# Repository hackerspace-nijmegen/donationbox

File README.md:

# donationbox

Arduino code was developed using plastformio. If you don't know it, I strongly recommend you to give it a try. If you just was to get this running quickly you can copy and paste the contents of main.cpp into the arduino ide. It is completely compatible. 

## Dependencies:
Arduino code depends on the [LowPower](https://github.com/rocketscream/Low-Power) library

## Circuit boards:
There is a double sided (arduinoshield) and a single sided version (arduinoshield-ss) of the same schematic. KiCad did not allow me to share the schematic between two boards so there is some duplication.
Neither is actually a shield. It's just a breakout board for a transistor switched led strip and two ir endstops. 

## Todo's:
* make a fancy animation (using pwm?) on the led instead of the current dump on/off sequence.

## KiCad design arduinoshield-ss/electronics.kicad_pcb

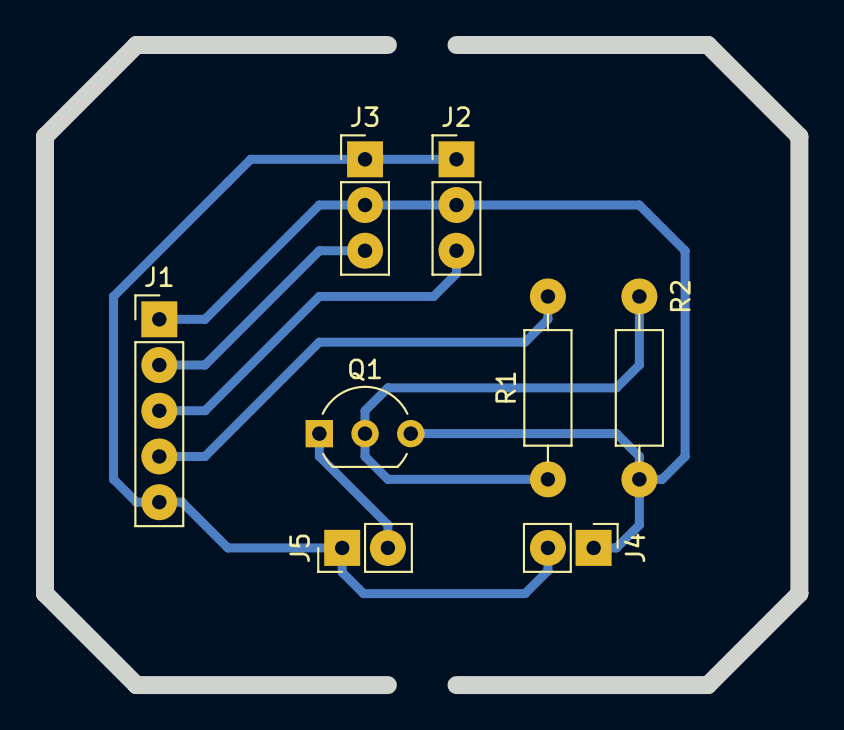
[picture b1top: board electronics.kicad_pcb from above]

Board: 2 copper layers, 41.9 x 35.6 mm, 8 parts (0 on the bottom side), 7 nets.

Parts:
J1: arduino; Pin_Header_Straight_1x05_Pitch2.54mm
J2: opt2; Pin_Header_Straight_1x03_Pitch2.54mm
J3: opt1; Pin_Header_Straight_1x03_Pitch2.54mm
J4: Bat; Pin_Header_Straight_1x02_Pitch2.54mm
J5: Led; Pin_Header_Straight_1x02_Pitch2.54mm
Q1: BC337; TO-92_Inline_Wide
R1: 470; R_Axial_DIN0207_L6.3mm_D2.5mm_P10.16mm_Horizontal
R2: 1k; R_Axial_DIN0207_L6.3mm_D2.5mm_P10.16mm_Horizontal

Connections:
GND: J1.1, J2.2, J3.2, J4.1, Q1.3, R2.2
unnamed: J1.2, J3.3
unnamed: J1.3, J2.3
unnamed: J1.4, R1.2
unnamed: J5.2, Q1.1
unnamed: Q1.2, R1.1, R2.1
VDD: J1.5, J2.1, J3.1, J4.2, J5.1

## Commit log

2018-05-31 initial git upload
